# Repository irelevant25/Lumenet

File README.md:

# Lumenet

A lighting desk in the browser, in the old style with faders, and **dmxbox**: a small box that takes what the
desk sends over USB to the DMX512 cable of the lights.

## What it does

* **Faders for 1 to 8 universes** of 512 channels, a page at a time, and **128 memories**: looks stored from the
  faders, each with a fader of its own. Keys under the faders, independents at the side, a master, blackout,
  solo up and down, and a rate for everything that runs.
* **Several boxes at once**, each output playing a universe: by themselves, or as the project says. Besides
  the box, **Art-Net** nodes, **sACN** and DMX USB interfaces of the kind of the **Enttec DMX USB Pro** play the
  universes as well.
* **Sequences**, made by hand or from a template (chase, wave, strobe, fire, storm), and a **stack**: the cues
  of a show with their fades and waits, played one after the other with GO, or at moments of the music;
  a cue sheet to print.
* **Effects** worked out live from a shape: circles and swings of moving heads, chases and pulses, rainbows
  and color chases, and patterns over the cells of LED bars by where they are on the stage. Each has a key and
  a fader, live speed, size and spread, and a preview; on Main and in the stack too.
* **Sounds:** music and other sounds from files, mixed by the desk program and played on a sound device of the
  PC, each with a key and a fader, its own level in decibels, fades, pan, speed, pitch, echo and reverb; a
  volume for all, MUTE and LISTEN on a second device; in the stack and in sequences, where a sound can play on
  through the steps after it until its end or a release. Beside them the tracks of the USB stick of a
  Soundcraft Ui mixer, played on the mixer's own player, its PLAYER channel the volume of all sounds and MUTE,
  both ways; the desk finds the mixer in the network by itself.
* **Fixtures:** lights by their kind, taken from the Open Fixture Library (666 lights) or the library of QLC+
  (1,781), played by intensity and color, moving heads by pan and tilt too; groups with one fader for all their
  lights.
* **Stage:** a plan of the rig with every light in its live color, a strobe flashing too.
* **Projects** in files, with notes for the show, undo and redo, an autosave, and backups into a folder that
  Google Drive, OneDrive or Dropbox syncs; export and import as one ZIP, and import of the show files of
  theatre consoles (USITT ASCII).
* **Phones and tablets** in the same network can use the desk as well, with a password.
* **MIDI controllers** play the desk: their keys press its keys, their faders and knobs move its faders, and
  the desk lights their keys and moves their motorized faders. Learn maps a control in two presses; the Akai
  APC mini mk2, Korg nanoKONTROL2 and Behringer X-Touch Mini and Compact have ready-made mappings. Other
  programs such as QLab and TouchOSC work the same keys and faders with **OSC**.
* A keyboard shortcut for every key, the usual ones from the start, and settings for how each device shows
  the desk, with a setup by the kind of show on the first start.
* **Ten example shows** to start from, from a few looks and cues to a whole concert, one of effects, two of
  sounds and one whose cues come on the music.

The desk also works without the box, on other DMX hardware or none. The box speaks Art-Net too, so other
lighting software such as QLC+ can use it.

## What it runs on

**The desk** runs on Windows 10 and 11 (64-bit), and its page in a current browser. With LAN switched on in
the page, phones and tablets in the same network can use it too: they get the same page, laid out for their
screen, and get in with a password.

**The boxes:** four dmxboxes bring the desk to DMX. Each is a USB network adapter for the computer, which
Windows, macOS and Linux take without a driver, and the desk finds it by itself. One USB cable powers it and
carries the data.

| | <br>[**Box 1**](boxes/box1/README.md)<br>Pico | <br>[**Box 2**](boxes/box2/README.md)<br>PIC32 | <br>[**Box 3**](boxes/box3/README.md)<br>RP2040 | <br>[**Box 4**](boxes/box4/README.md)<br>RP2040 |
|---|:---:|:---:|:---:|:---:|
| Isolated DMX output | ✅ | ✅ | ✅ | ✅ |
| RDM: sets up the lights | ✅ | ✅ | ✅ | ✅ |
| Number switch, for several boxes | ✅ | ✅ | ✅ | ✅ |
| USB-C | ❌ | ✅ | ✅ | ✅ |
| DMX IN: a console plays the desk | ❌ | ❌ | ❌ | ✅ |
| MIDI IN and OUT | ❌ | ❌ | ❌ | ✅ |
| USB OUT to the next box | ❌ | ❌ | ❌ | ✅ |
| POWER socket for a charger | ❌ | ❌ | ❌ | ✅ |
| Update firmware over USB | ✅ | ❌ | ✅ | ✅ |
| Assembly | THT | THT | SMD | SMD |
| Soldered by external company | ❌ | ❌ | ✅ | ✅ |
| Case | 3D printed | 3D printed | 3D printed | Aluminium or 3D printed |

The pictures are renders of the designs; none of the four has been built yet. The first box 1, a
Raspberry Pi Pico on a perfboard, was built and works with the desk.

## Get it

**Download:** `Lumenet.exe` from the newest release on the [Releases](../../releases) page. It is the whole desk in
one file, with nothing to install. Start it: the page opens in the browser, and Lumenet sits in the
notification area of the taskbar, where its menu opens the page again, shows the log, and ends it. Windows may
say that it does not know the program, as it is not signed: More info, then Run anyway. Later versions come
from the desk itself: Settings, About, says when one is out and puts it in place at a press.

**From the sources:** with the .NET 10 SDK and Node.js 22, `run.cmd` starts the desk; then open
http://localhost:4200. `sim.cmd` starts a simulated box, Art-Net node, sACN receiver or USB interface for the
desk to play on, or a MIDI controller to play it with, without the hardware (see
[DEV.md](DEV.md#simulated-devices-simcmd)).

**A box:** what to order and what to buy and fit yourself is in each box's BOM.md, for example
[box 4's](boxes/box4/BOM.md); the schematics, the boards and the firmware are in [DEV.md](DEV.md#1-hardware), and
all four boxes in [boxes/](boxes/README.md).

## More

* [MANUAL.md](MANUAL.md): every view, key and setting of the desk.
* [DEV.md](DEV.md): the box's hardware and firmware, the PC side, how the desk is built and tested, the DX
  protocol, and what has been tried so far.

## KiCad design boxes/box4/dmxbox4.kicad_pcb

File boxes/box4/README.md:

# Box 4: dmxbox 4, the full box

An RP2040 behind a USB hub: IN from the computer, OUT for the next box, POWER for a charger, one DMX output with
RDM, a DMX input (a console plays the desk), MIDI IN and OUT, and the box-number switch. Every part sits on the top side, and JLCPCB solders them all.
Until 2026-11-28 it was called dmxbox 3. How it works: [DEV.md](../../DEV.md#1-hardware).

| File or folder | What |
|---|---|
| [BOM.md](BOM.md) | What to order and buy, how to print the case and put the box together |
| `jlcpcb/` | The Gerber ZIP, the BOM and the placement file for JLCPCB |
| `dmxbox4_schematic.pdf`, `dmxbox4_assembly.pdf`, `dmxbox4_copper.pdf` | The drawings |
| `case_print/` | The case printed in PETG: STL files for the slicer |
| `case/` | JLCMC's aluminium case (K119-12063-H7-L130) with its holes, instead |
| `3d/` | The Blender model and the pictures |
| `firmware/` | `box.h` and `dmxbox4.h` make the shared RP2040 firmware box 4's; `build.cmd` builds `dmxbox4.uf2`, `flash.cmd` puts it onto a box |
| `dmxbox4.kicad_*`, `dmxbox4.pretty/` | The KiCad project, made by the scripts |
| `scripts/` | Make the board, the drawings, the pictures and the cases from `circuit.py` |

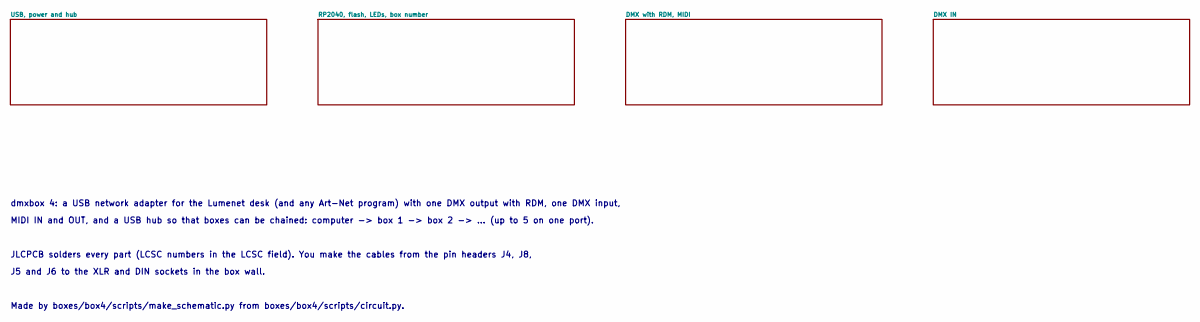
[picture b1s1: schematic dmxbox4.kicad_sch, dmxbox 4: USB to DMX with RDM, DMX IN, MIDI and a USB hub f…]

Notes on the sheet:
dmxbox 4: a USB network adapter for the Lumenet desk (and any Art-Net program) with one DMX output with RDM, one DMX input,
MIDI IN and OUT, and a USB hub so that boxes can be chained: computer -> box 1 -> box 2 -> ... (up to 5 on one port).
JLCPCB solders every part (LCSC numbers in the LCSC field). You make the cables from the pin headers J4, J8,
J5 and J6 to the XLR and DIN sockets in the box wall.
Made by boxes/box4/scripts/make_schematic.py from boxes/box4/scripts/circuit.py.

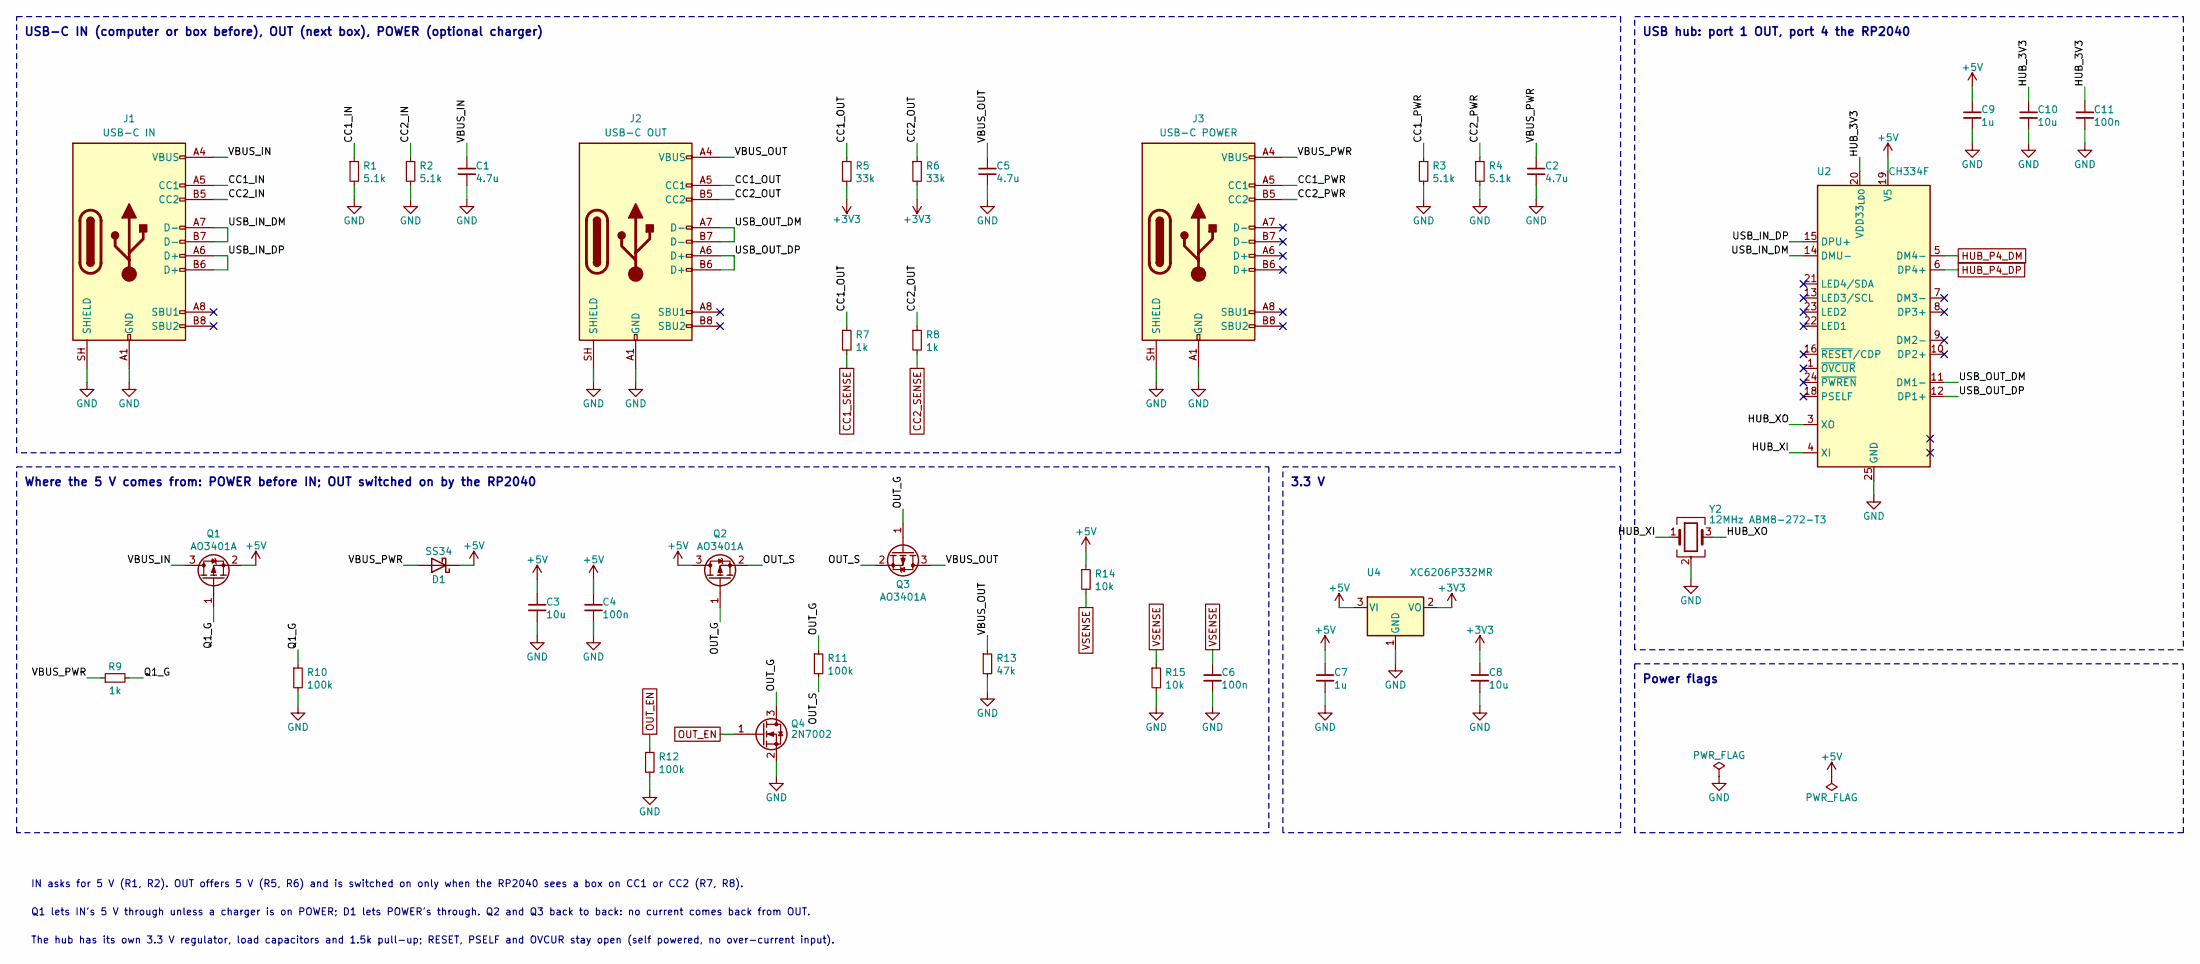
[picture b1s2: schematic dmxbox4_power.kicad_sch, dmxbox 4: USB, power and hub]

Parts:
C1, C2, C5: 4.7u; C_0603_1608Metric; LCSC C19666
C3: 10u; C_0805_2012Metric; LCSC C15850
C4, C6, C11: 100n; C_0603_1608Metric; LCSC C14663
C7, C9: 1u; C_0603_1608Metric; LCSC C15849
C8, C10: 10u; C_0603_1608Metric; LCSC C19702
D1: SS34; D_SMA; LCSC C8678
J1: USB-C IN; USB_C_Receptacle_HRO_TYPE-C-31-M-12; LCSC C165948
J2: USB-C OUT; USB_C_Receptacle_HRO_TYPE-C-31-M-12; LCSC C165948
J3: USB-C POWER; USB_C_Receptacle_HRO_TYPE-C-31-M-12; LCSC C165948
Q1, Q2, Q3: AO3401A; SOT-23; LCSC C15127
Q4: 2N7002; SOT-23; LCSC C8545
R1, R2, R3, R4: 5.1k; R_0603_1608Metric; LCSC C23186
R5, R6: 33k; R_0603_1608Metric; LCSC C4216
R7, R8, R9: 1k; R_0603_1608Metric; LCSC C21190
R10, R11, R12: 100k; R_0603_1608Metric; LCSC C25803
R13: 47k; R_0603_1608Metric; LCSC C25819
R14, R15: 10k; R_0603_1608Metric; LCSC C25804
U2: CH334F; QFN-24-1EP_4x4mm_P0.5mm_EP2.7x2.7mm; LCSC C5187527
U4: XC6206P332MR; SOT-23-3; LCSC C5446
Y2: 12MHz ABM8-272-T3; Crystal_SMD_3225-4Pin_3.2x2.5mm; LCSC C20625731

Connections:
+3V3: C8.1, R5.2, R6.2, U4.2 (VO); also elsewhere on the board
+5V: C3.1, C4.1, C7.1, C9.1, D1.1 (K), Q1.2 (S), Q2.3 (D), R14.1, U2.19 (V5), U4.3 (VI); also elsewhere on the board
/USB, power and hub/CC1_IN: J1.A5 (CC1), R1.1
/USB, power and hub/CC1_OUT: J2.A5 (CC1), R5.1, R7.1
/USB, power and hub/CC1_PWR: J3.A5 (CC1), R3.1
/USB, power and hub/CC2_IN: J1.B5 (CC2), R2.1
/USB, power and hub/CC2_OUT: J2.B5 (CC2), R6.1, R8.1
/USB, power and hub/CC2_PWR: J3.B5 (CC2), R4.1
/USB, power and hub/HUB_3V3: C10.1, C11.1, U2.20 (VDD33_{LDO})
/USB, power and hub/HUB_XI: U2.4 (XI), Y2.1
/USB, power and hub/HUB_XO: U2.3 (XO), Y2.3
/USB, power and hub/OUT_G: Q2.1 (G), Q3.1 (G), Q4.3 (D), R11.1
/USB, power and hub/OUT_S: Q2.2 (S), Q3.2 (S), R11.2
/USB, power and hub/Q1_G: Q1.1 (G), R9.2, R10.1
/USB, power and hub/USB_IN_DM: J1.A7 (D-), J1.B7 (D-), U2.14 (DMU-)
/USB, power and hub/USB_IN_DP: J1.A6 (D+), J1.B6 (D+), U2.15 (DPU+)
/USB, power and hub/USB_OUT_DM: J2.A7 (D-), J2.B7 (D-), U2.11 (DM1-)
/USB, power and hub/USB_OUT_DP: J2.A6 (D+), J2.B6 (D+), U2.12 (DP1+)
/USB, power and hub/VBUS_IN: C1.1, J1.A4 (VBUS), J1.A9 (VBUS), J1.B4 (VBUS), J1.B9 (VBUS), Q1.3 (D)
/USB, power and hub/VBUS_OUT: C5.1, J2.A4 (VBUS), J2.A9 (VBUS), J2.B4 (VBUS), J2.B9 (VBUS), Q3.3 (D), R13.1
/USB, power and hub/VBUS_PWR: C2.1, D1.2 (A), J3.A4 (VBUS), J3.A9 (VBUS), J3.B4 (VBUS), J3.B9 (VBUS), R9.1
CC1_SENSE: R7.2; also elsewhere on the board
CC2_SENSE: R8.2; also elsewhere on the board
GND: C1.2, C2.2, C3.2, C4.2, C5.2, C6.2, C7.2, C8.2, C9.2, C10.2, C11.2, J1.A1 (GND), J1.A12 (GND), J1.B1 (GND), J1.B12 (GND), J1.SH (SHIELD), J2.A1 (GND), J2.A12 (GND), J2.B1 (GND), J2.B12 (GND), J2.SH (SHIELD), J3.A1 (GND), J3.A12 (GND), J3.B1 (GND), J3.B12 (GND), J3.SH (SHIELD), Q4.2 (S), R1.2, R2.2, R3.2, R4.2, R10.2, R12.2, R13.2, R15.2, U2.25 (GND), U4.1 (GND), Y2.2 (G), Y2.4 (G); also elsewhere on the board
HUB_P4_DM: U2.5 (DM4-); also elsewhere on the board
HUB_P4_DP: U2.6 (DP4+); also elsewhere on the board
OUT_EN: Q4.1 (G), R12.1; also elsewhere on the board
VSENSE: C6.1, R14.2, R15.1; also elsewhere on the board

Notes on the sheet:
USB-C IN (computer or box before), OUT (next box), POWER (optional charger)
Where the 5 V comes from: POWER before IN; OUT switched on by the RP2040
3.3 V
USB hub: port 1 OUT, port 4 the RP2040
Power flags
IN asks for 5 V (R1, R2). OUT offers 5 V (R5, R6) and is switched on only when the RP2040 sees a box on CC1 or CC2 (R7, R8).
Q1 lets IN's 5 V through unless a charger is on POWER; D1 lets POWER's through. Q2 and Q3 back to back: no current comes back from OUT.
The hub has its own 3.3 V regulator, load capacitors and 1.5k pull-up; RESET, PSELF and OVCUR stay open (self powered, no over-current input).

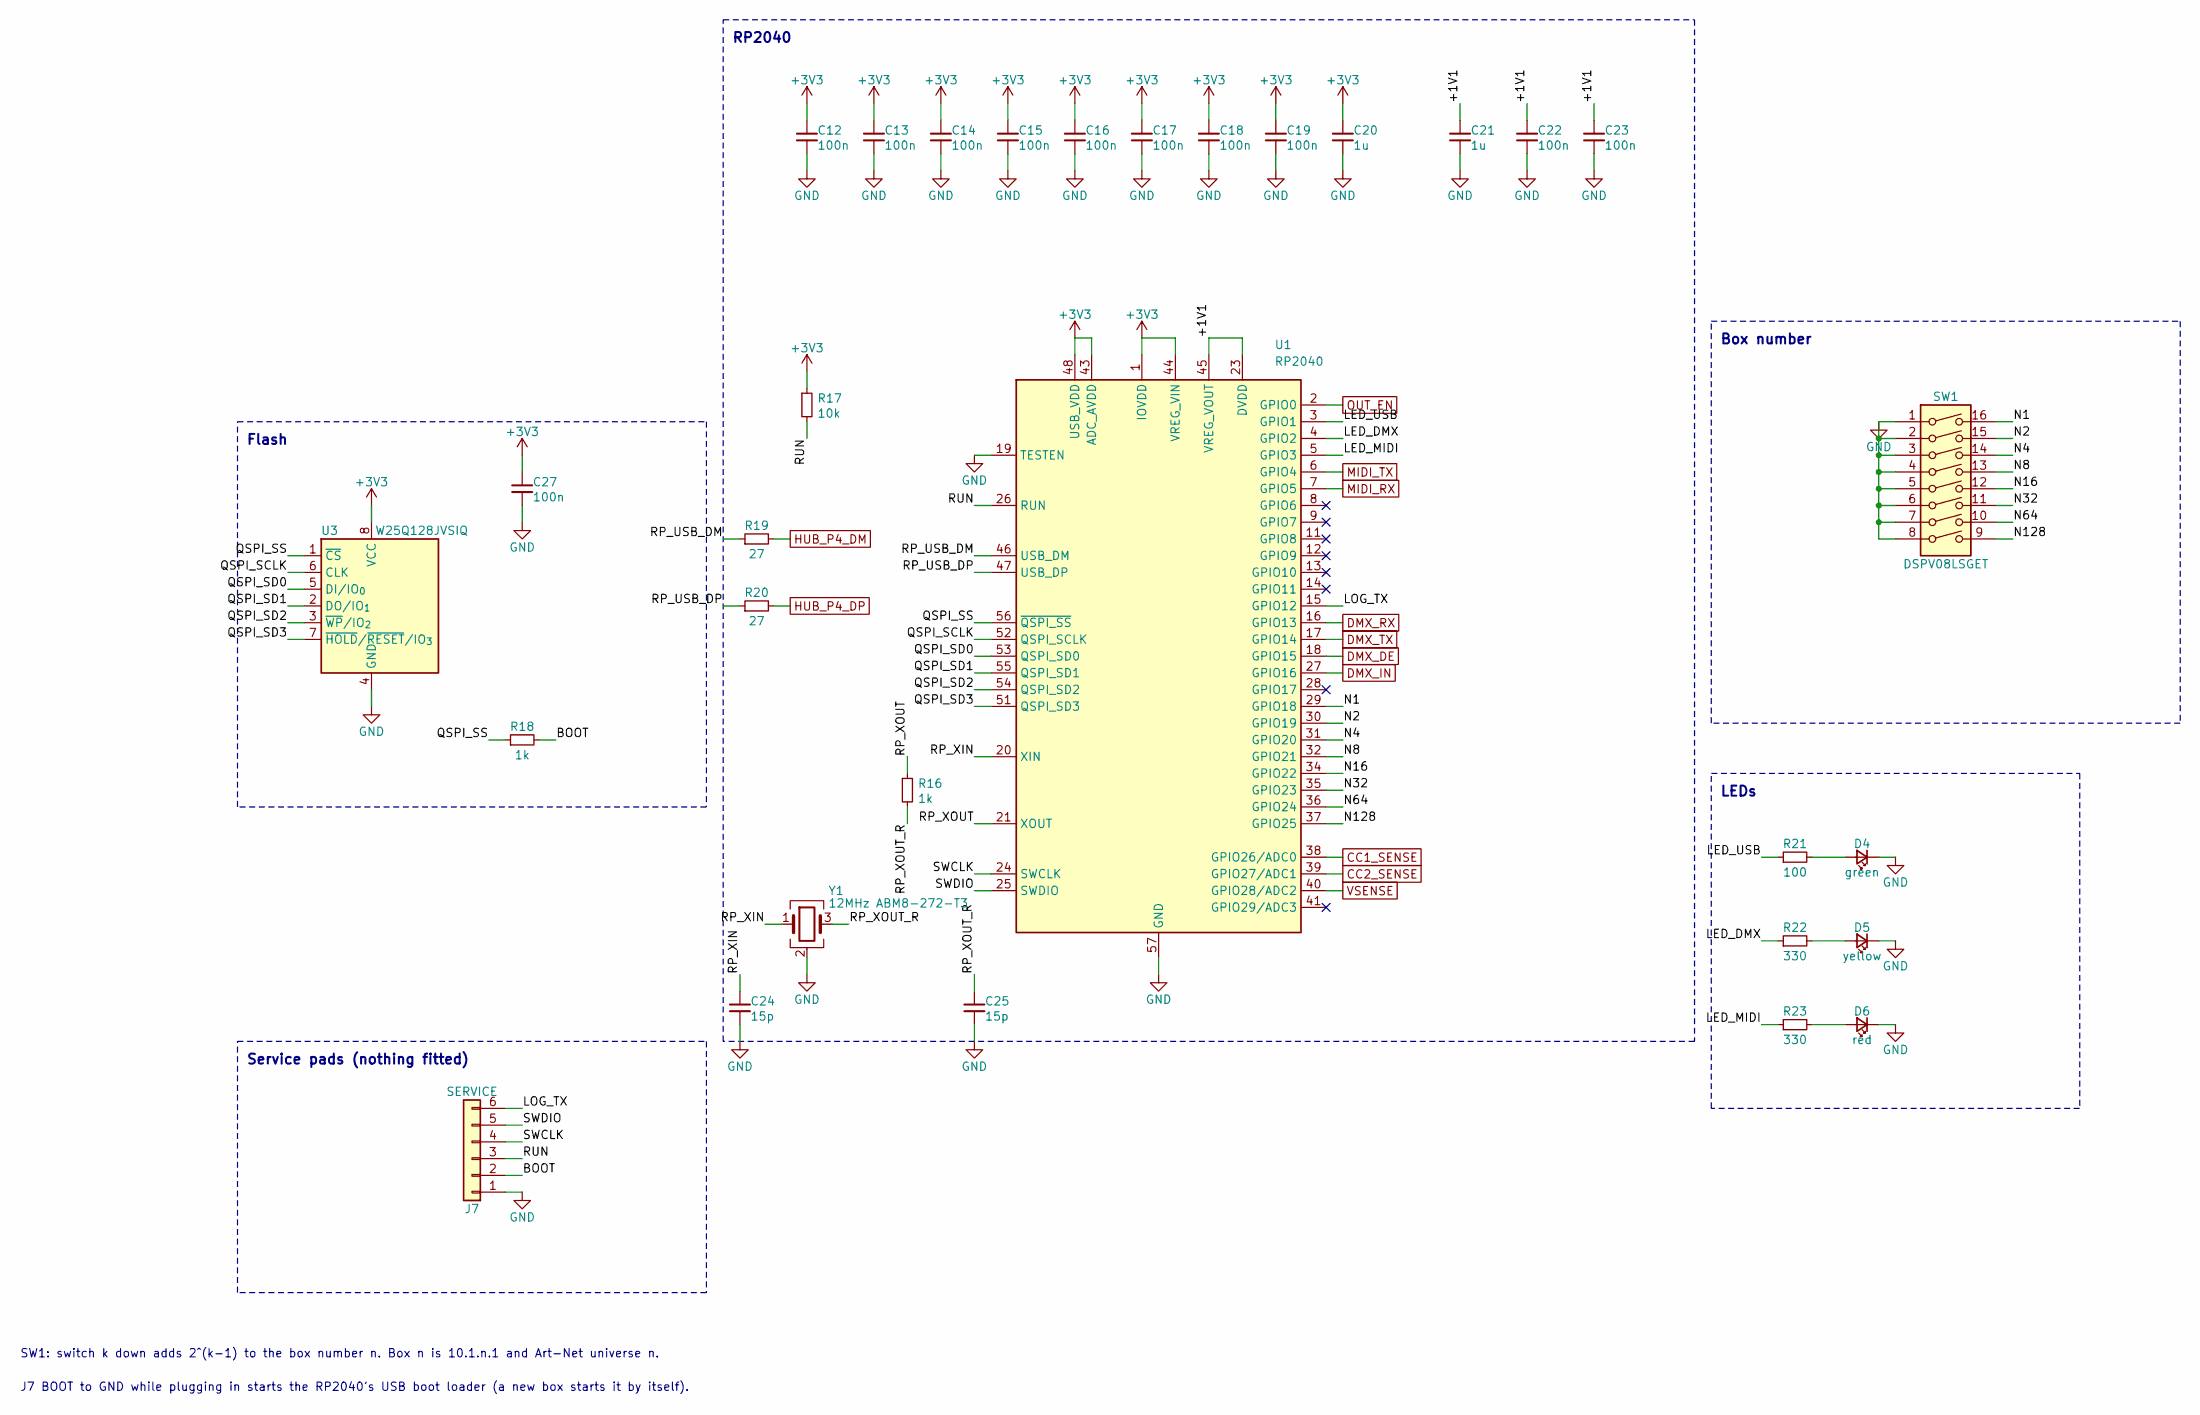
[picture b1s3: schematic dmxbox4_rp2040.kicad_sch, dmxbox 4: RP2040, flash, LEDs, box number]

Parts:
C12, C13, C14, C15, C16, C17, C18, C19, C22, C23, C27: 100n; C_0603_1608Metric; LCSC C14663
C20, C21: 1u; C_0603_1608Metric; LCSC C15849
C24, C25: 15p; C_0603_1608Metric; LCSC C1644
D4: green; LED_0805_2012Metric; LCSC C2297
D5: yellow; LED_0805_2012Metric; LCSC C2296
D6: red; LED_0805_2012Metric; LCSC C84256
J7: SERVICE; PinSocket_1x06_P2.54mm_Vertical_SMD_BothSides; LCSC C42380984
R16, R18: 1k; R_0603_1608Metric; LCSC C21190
R17: 10k; R_0603_1608Metric; LCSC C25804
R19, R20: 27; R_0603_1608Metric; LCSC C25190
R21: 100; R_0603_1608Metric; LCSC C22775
R22, R23: 330; R_0603_1608Metric; LCSC C23138
SW1: DSPV08LSGET; SW_DIP_SPSTx08_Piano_Kangshen_DSPV08LSGET_P2.54mm; LCSC C3293170
U1: RP2040; QFN-56-1EP_7x7mm_P0.4mm_EP3.2x3.2mm; LCSC C2040
U3: W25Q128JVSIQ; SOIC-8_5.3x5.3mm_P1.27mm; LCSC C97521
Y1: 12MHz ABM8-272-T3; Crystal_SMD_3225-4Pin_3.2x2.5mm; LCSC C20625731

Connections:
+3V3: C12.1, C13.1, C14.1, C15.1, C16.1, C17.1, C18.1, C19.1, C20.1, C27.1, R17.1, U1.1 (IOVDD), U1.10 (IOVDD), U1.22 (IOVDD), U1.33 (IOVDD), U1.42 (IOVDD), U1.43 (ADC_AVDD), U1.44 (VREG_VIN), U1.48 (USB_VDD), U1.49 (IOVDD), U3.8 (VCC); also elsewhere on the board
/RP2040, flash, LEDs, box number/+1V1: C21.1, C22.1, C23.1, U1.23 (DVDD), U1.45 (VREG_VOUT), U1.50 (DVDD)
/RP2040, flash, LEDs, box number/BOOT: J7.2, R18.2
/RP2040, flash, LEDs, box number/LED_DMX: R22.1, U1.4 (GPIO2)
/RP2040, flash, LEDs, box number/LED_MIDI: R23.1, U1.5 (GPIO3)
/RP2040, flash, LEDs, box number/LED_USB: R21.1, U1.3 (GPIO1)
/RP2040, flash, LEDs, box number/LOG_TX: J7.6, U1.15 (GPIO12)
/RP2040, flash, LEDs, box number/N1: SW1.16, U1.29 (GPIO18)
/RP2040, flash, LEDs, box number/N2: SW1.15, U1.30 (GPIO19)
/RP2040, flash, LEDs, box number/N4: SW1.14, U1.31 (GPIO20)
/RP2040, flash, LEDs, box number/N8: SW1.13, U1.32 (GPIO21)
/RP2040, flash, LEDs, box number/N16: SW1.12, U1.34 (GPIO22)
/RP2040, flash, LEDs, box number/N32: SW1.11, U1.35 (GPIO23)
/RP2040, flash, LEDs, box number/N64: SW1.10, U1.36 (GPIO24)
/RP2040, flash, LEDs, box number/N128: SW1.9, U1.37 (GPIO25)
/RP2040, flash, LEDs, box number/QSPI_SCLK: U1.52 (QSPI_SCLK), U3.6 (CLK)
/RP2040, flash, LEDs, box number/QSPI_SD0: U1.53 (QSPI_SD0), U3.5 (DI/IO_{0})
/RP2040, flash, LEDs, box number/QSPI_SD1: U1.55 (QSPI_SD1), U3.2 (DO/IO_{1})
/RP2040, flash, LEDs, box number/QSPI_SD2: U1.54 (QSPI_SD2), U3.3 (~WP/IO_{2})
/RP2040, flash, LEDs, box number/QSPI_SD3: U1.51 (QSPI_SD3), U3.7 (~HOLD/~RESET/IO_{3})
/RP2040, flash, LEDs, box number/QSPI_SS: R18.1, U1.56 (~QSPI_SS), U3.1 (~CS)
/RP2040, flash, LEDs, box number/RP_USB_DM: R19.1, U1.46 (USB_DM)
/RP2040, flash, LEDs, box number/RP_USB_DP: R20.1, U1.47 (USB_DP)
/RP2040, flash, LEDs, box number/RP_XIN: C24.1, U1.20 (XIN), Y1.1
/RP2040, flash, LEDs, box number/RP_XOUT: R16.1, U1.21 (XOUT)
/RP2040, flash, LEDs, box number/RP_XOUT_R: C25.1, R16.2, Y1.3
/RP2040, flash, LEDs, box number/RUN: J7.3, R17.2, U1.26 (RUN)
/RP2040, flash, LEDs, box number/SWCLK: J7.4, U1.24 (SWCLK)
/RP2040, flash, LEDs, box number/SWDIO: J7.5, U1.25 (SWDIO)
CC1_SENSE: U1.38 (GPIO26/ADC0); also elsewhere on the board
CC2_SENSE: U1.39 (GPIO27/ADC1); also elsewhere on the board
DMX_DE: U1.18 (GPIO15); also elsewhere on the board
DMX_IN: U1.27 (GPIO16); also elsewhere on the board
DMX_RX: U1.16 (GPIO13); also elsewhere on the board
DMX_TX: U1.17 (GPIO14); also elsewhere on the board
GND: C12.2, C13.2, C14.2, C15.2, C16.2, C17.2, C18.2, C19.2, C20.2, C21.2, C22.2, C23.2, C24.2, C25.2, C27.2, D4.1 (K), D5.1 (K), D6.1 (K), J7.1, SW1.1, SW1.2, SW1.3, SW1.4, SW1.5, SW1.6, SW1.7, SW1.8, U1.19 (TESTEN), U1.57 (GND), U3.4 (GND), Y1.2 (G), Y1.4 (G); also elsewhere on the board
HUB_P4_DM: R19.2; also elsewhere on the board
HUB_P4_DP: R20.2; also elsewhere on the board
MIDI_RX: U1.7 (GPIO5); also elsewhere on the board
MIDI_TX: U1.6 (GPIO4); also elsewhere on the board
unnamed: D4.2 (A), R21.2
unnamed: D5.2 (A), R22.2
unnamed: D6.2 (A), R23.2
OUT_EN: U1.2 (GPIO0); also elsewhere on the board
VSENSE: U1.40 (GPIO28/ADC2); also elsewhere on the board

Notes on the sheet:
RP2040
Flash
Service pads (nothing fitted)
LEDs
Box number
SW1: switch k down adds 2^(k-1) to the box number n. Box n is 10.1.n.1 and Art-Net universe n.
J7 BOOT to GND while plugging in starts the RP2040's USB boot loader (a new box starts it by itself).

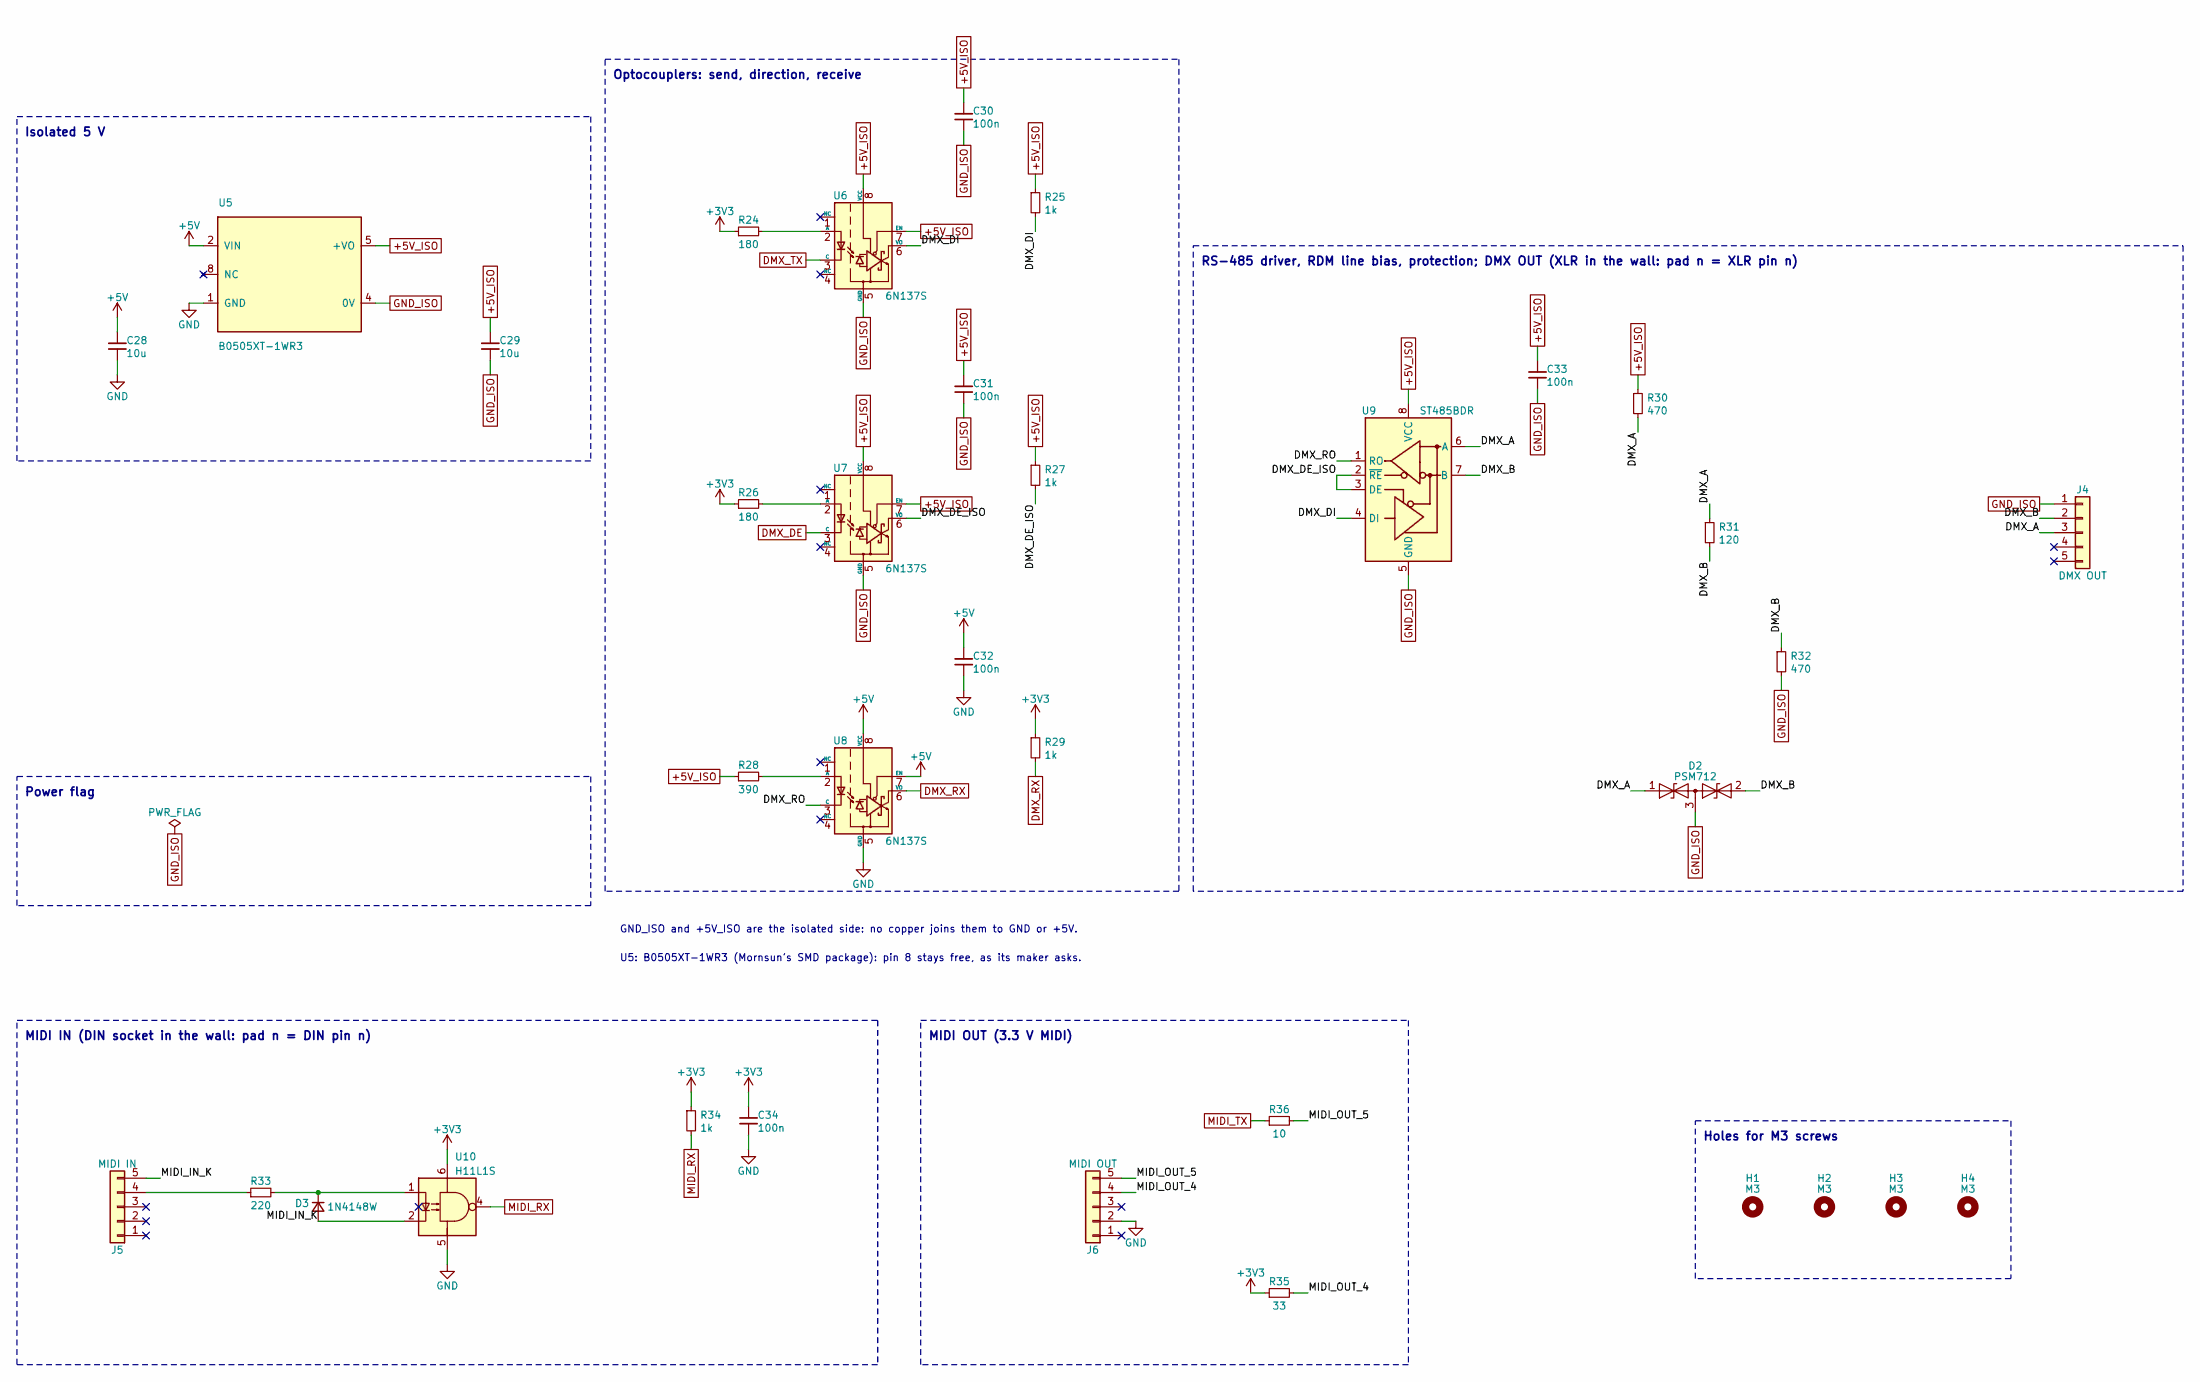
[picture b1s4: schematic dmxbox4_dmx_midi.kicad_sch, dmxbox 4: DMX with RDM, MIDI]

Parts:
C28, C29: 10u; C_0805_2012Metric; LCSC C15850
C30, C31, C32, C33, C34: 100n; C_0603_1608Metric; LCSC C14663
D2: PSM712; SOT-23; LCSC C32677
D3: 1N4148W; D_SOD-123; LCSC C81598
H1, H2, H3, H4: M3; MountingHole_3.2mm_M3
J4: DMX OUT; PinHeader_1x05_P2.54mm_Vertical_SMD_BothSides; LCSC C41417362
J5: MIDI IN; PinHeader_1x05_P2.54mm_Vertical_SMD_BothSides; LCSC C41417362
J6: MIDI OUT; PinHeader_1x05_P2.54mm_Vertical_SMD_BothSides; LCSC C41417362
R24, R26: 180; R_0603_1608Metric; LCSC C22828
R25, R27, R29, R34: 1k; R_0603_1608Metric; LCSC C21190
R28: 390; R_0603_1608Metric; LCSC C23151
R30, R32: 470; R_0603_1608Metric; LCSC C23179
R31: 120; R_1206_3216Metric; LCSC C17909
R33: 220; R_0603_1608Metric; LCSC C22962
R35: 33; R_0603_1608Metric; LCSC C23140
R36: 10; R_0603_1608Metric; LCSC C22859
U5: B0505XT-1WR3; Converter_DCDC_Mornsun_B05_XT-1WR3; LCSC C19188495
U6, U7, U8: 6N137S; SMDIP-8_W9.53mm; LCSC C92651
U9: ST485BDR; SOIC-8_3.9x4.9mm_P1.27mm; LCSC C91197
U10: H11L1S; SMDIP-6_W9.53mm; LCSC C78589

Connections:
+3V3: C34.1, R24.1, R26.1, R29.1, R34.1, R35.1, U10.6; also elsewhere on the board
+5V: C28.1, C32.1, U5.2 (VIN), U8.7 (EN), U8.8 (VCC); also elsewhere on the board
+5V_ISO: C29.1, C30.1, C31.1, C33.1, R25.1, R27.1, R28.1, R30.1, U5.5 (+VO), U6.7 (EN), U6.8 (VCC), U7.7 (EN), U7.8 (VCC), U9.8 (VCC); also elsewhere on the board
/DMX with RDM, MIDI/DMX_A: D2.1 (A1), J4.3, R30.2, R31.1, U9.6 (A)
/DMX with RDM, MIDI/DMX_B: D2.2 (A2), J4.2, R31.2, R32.1, U9.7 (B)
/DMX with RDM, MIDI/DMX_DE_ISO: R27.2, U7.6 (VO), U9.2 (~RE), U9.3 (DE)
/DMX with RDM, MIDI/DMX_DI: R25.2, U6.6 (VO), U9.4 (DI)
/DMX with RDM, MIDI/DMX_RO: U8.3 (C), U9.1 (RO)
/DMX with RDM, MIDI/MIDI_IN_K: D3.2 (A), J5.5, U10.2
/DMX with RDM, MIDI/MIDI_OUT_4: J6.4, R35.2
/DMX with RDM, MIDI/MIDI_OUT_5: J6.5, R36.2
DMX_DE: U7.3 (C); also elsewhere on the board
DMX_RX: R29.2, U8.6 (VO); also elsewhere on the board
DMX_TX: U6.3 (C); also elsewhere on the board
GND: C28.2, C32.2, C34.2, J6.2, U5.1 (GND), U8.5 (GND), U10.5; also elsewhere on the board
GND_ISO: C29.2, C30.2, C31.2, C33.2, D2.3 (common), J4.1, R32.2, U5.4 (0V), U6.5 (GND), U7.5 (GND), U9.5 (GND); also elsewhere on the board
MIDI_RX: R34.2, U10.4; also elsewhere on the board
MIDI_TX: R36.1; also elsewhere on the board
unnamed: D3.1 (K), R33.2, U10.1
unnamed: J5.4, R33.1
unnamed: R24.2, U6.2 (A)
unnamed: R26.2, U7.2 (A)
unnamed: R28.2, U8.2 (A)

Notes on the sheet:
Isolated 5 V
Optocouplers: send, direction, receive
RS-485 driver, RDM line bias, protection; DMX OUT (XLR in the wall: pad n = XLR pin n)
MIDI IN (DIN socket in the wall: pad n = DIN pin n)
MIDI OUT (3.3 V MIDI)
Holes for M3 screws
Power flag
GND_ISO and +5V_ISO are the isolated side: no copper joins them to GND or +5V.
U5: B0505XT-1WR3 (Mornsun's SMD package): pin 8 stays free, as its maker asks.

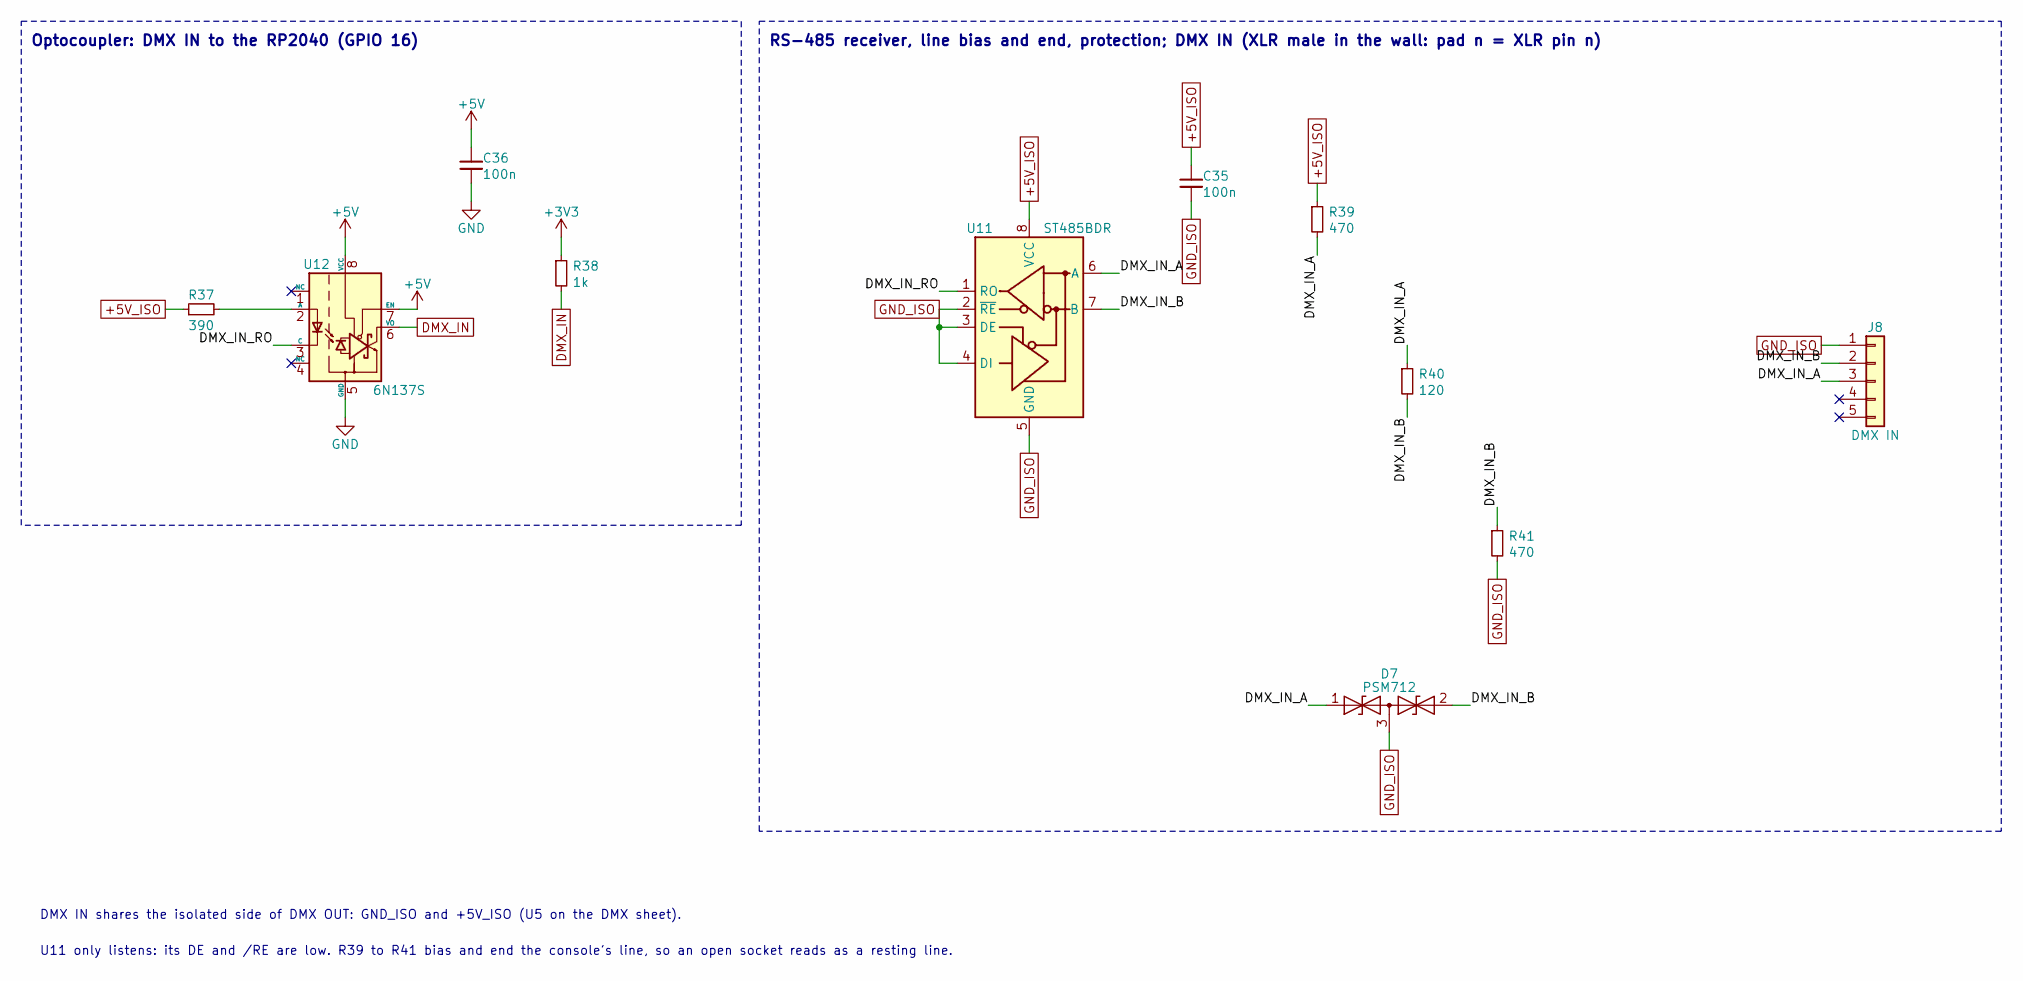
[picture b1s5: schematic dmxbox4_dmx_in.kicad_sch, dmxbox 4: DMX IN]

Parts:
C35, C36: 100n; C_0603_1608Metric; LCSC C14663
D7: PSM712; SOT-23; LCSC C32677
J8: DMX IN; PinHeader_1x05_P2.54mm_Vertical_SMD_BothSides; LCSC C41417362
R37: 390; R_0603_1608Metric; LCSC C23151
R38: 1k; R_0603_1608Metric; LCSC C21190
R39, R41: 470; R_0603_1608Metric; LCSC C23179
R40: 120; R_1206_3216Metric; LCSC C17909
U11: ST485BDR; SOIC-8_3.9x4.9mm_P1.27mm; LCSC C91197
U12: 6N137S; SMDIP-8_W9.53mm; LCSC C92651

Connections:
+3V3: R38.1; also elsewhere on the board
+5V: C36.1, U12.7 (EN), U12.8 (VCC); also elsewhere on the board
+5V_ISO: C35.1, R37.1, R39.1, U11.8 (VCC); also elsewhere on the board
/DMX IN/DMX_IN_A: D7.1 (A1), J8.3, R39.2, R40.1, U11.6 (A)
/DMX IN/DMX_IN_B: D7.2 (A2), J8.2, R40.2, R41.1, U11.7 (B)
/DMX IN/DMX_IN_RO: U11.1 (RO), U12.3 (C)
DMX_IN: R38.2, U12.6 (VO); also elsewhere on the board
GND: C36.2, U12.5 (GND); also elsewhere on the board
GND_ISO: C35.2, D7.3 (common), J8.1, R41.2, U11.2 (~RE), U11.3 (DE), U11.4 (DI), U11.5 (GND); also elsewhere on the board
unnamed: R37.2, U12.2 (A)

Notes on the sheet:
Optocoupler: DMX IN to the RP2040 (GPIO 16)
RS-485 receiver, line bias and end, protection; DMX IN (XLR male in the wall: pad n = XLR pin n)
DMX IN shares the isolated side of DMX OUT: GND_ISO and +5V_ISO (U5 on the DMX sheet).
U11 only listens: its DE and /RE are low. R39 to R41 bias and end the console's line, so an open socket reads as a resting line.
